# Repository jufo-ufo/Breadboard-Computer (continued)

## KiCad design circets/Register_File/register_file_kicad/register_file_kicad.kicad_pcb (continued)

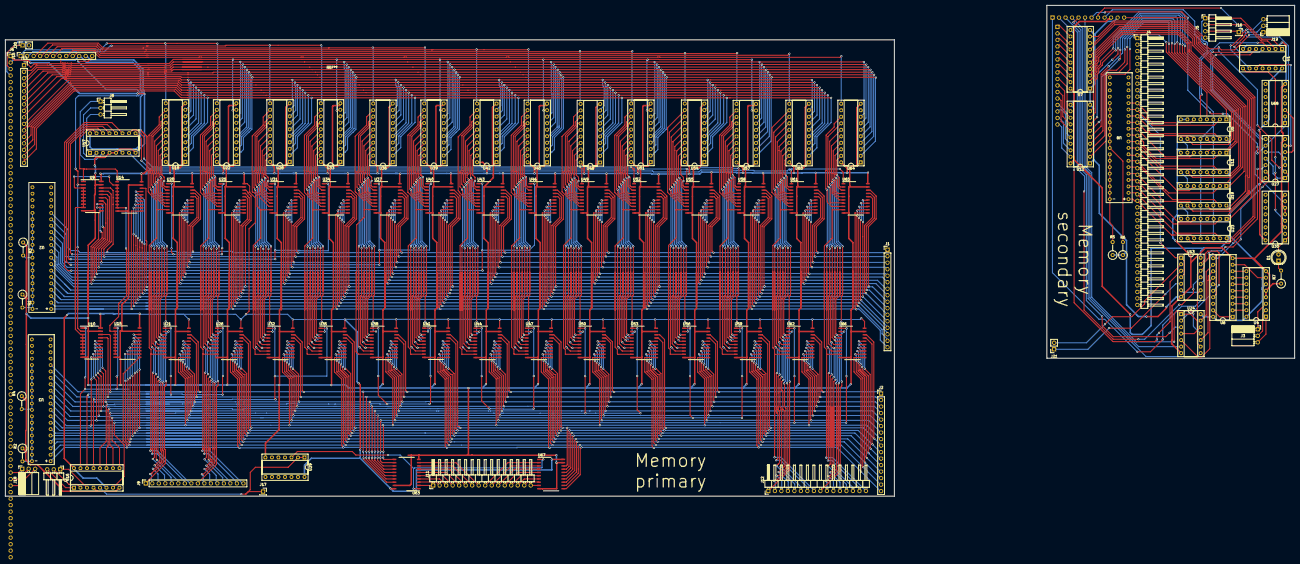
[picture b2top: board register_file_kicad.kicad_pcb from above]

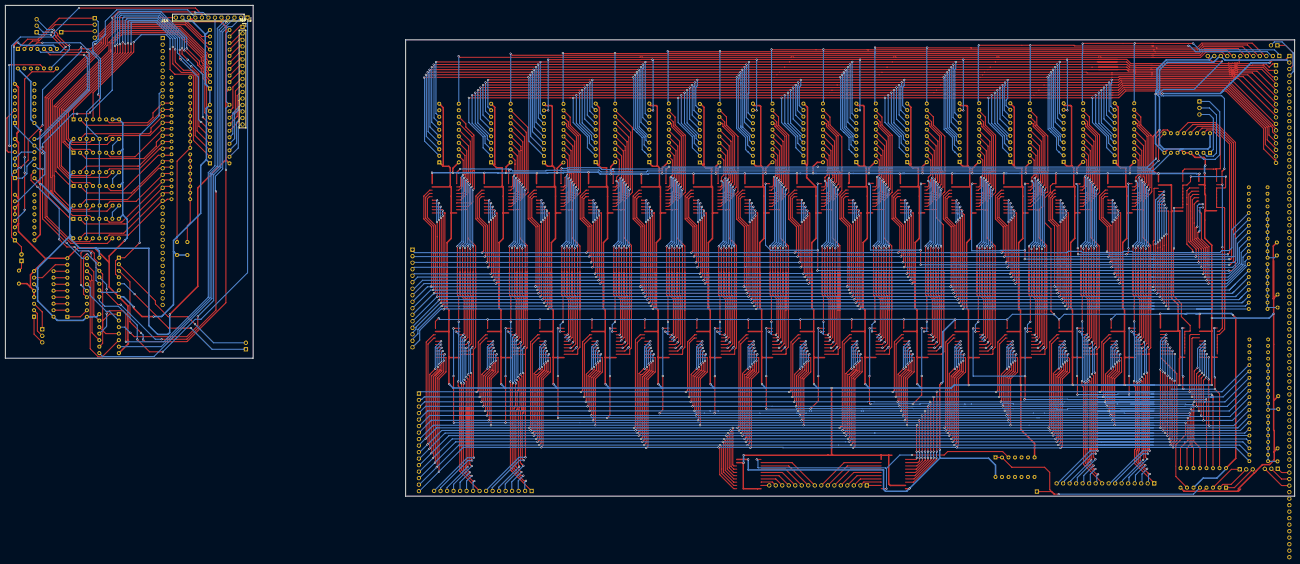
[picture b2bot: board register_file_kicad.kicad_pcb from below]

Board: 2 copper layers, 503.1 x 191.5 mm, 97 parts (2 on the bottom side), 321 nets.

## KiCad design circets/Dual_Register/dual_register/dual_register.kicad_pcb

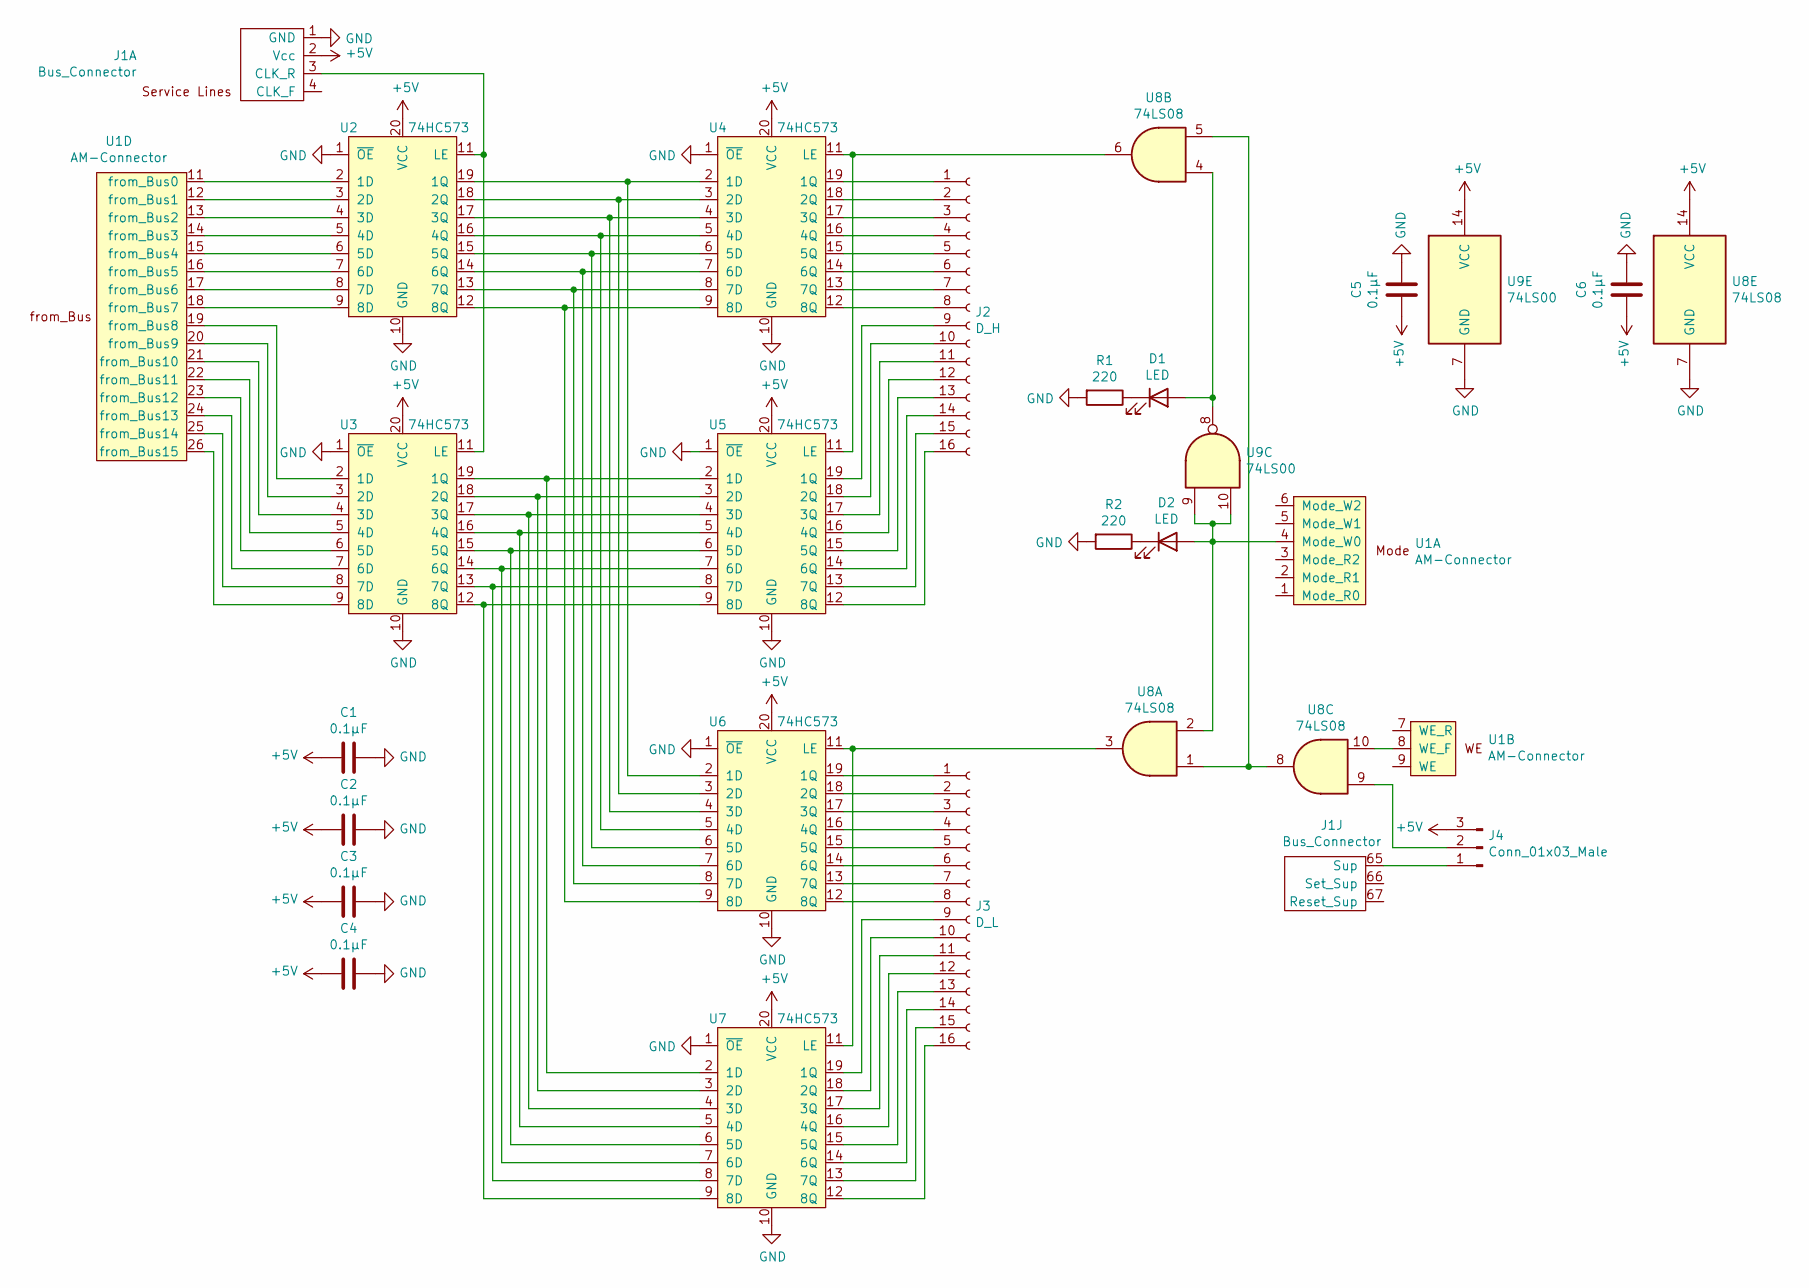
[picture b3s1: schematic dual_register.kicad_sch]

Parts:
C1, C2, C3, C4, C5, C6: 0.1µF; C_Disc_D8.0mm_W5.0mm_P5.00mm
D1, D2: LED; LED_D5.0mm
J1: Bus_Connector; PinHeader_1x78_P2.54mm_Horizontal
J2: D_H; PinHeader_1x16_P2.00mm_Vertical
J3: D_L; PinHeader_1x16_P2.00mm_Vertical
J4: Conn_01x03_Male; PinSocket_1x03_P2.00mm_Vertical
R1, R2: 220; R_Axial_DIN0309_L9.0mm_D3.2mm_P2.54mm_Vertical
U1: AM-Connector; PinHeader_1x42_P2.54mm_Horizontal
U2, U3, U4, U5, U6, U7: 74HC573; DIP-20_W7.62mm_Socket
U8: 74LS08; DIP-14_W7.62mm_Socket
U9: 74LS00; DIP-14_W7.62mm_Socket

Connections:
+5V: C1.2, C2.2, C3.2, C4.2, C5.2, C6.2, J1.2 (Vcc), J4.3, U2.20 (VCC), U3.20 (VCC), U4.20 (VCC), U5.20 (VCC), U6.20 (VCC), U7.20 (VCC), U8.14 (VCC), U9.14 (VCC)
GND: C1.1, C2.1, C3.1, C4.1, C5.1, C6.1, J1.1 (GND), R1.2, R2.2, U2.1 (~OE), U2.10 (GND), U3.1 (~OE), U3.10 (GND), U4.1 (~OE), U4.10 (GND), U5.1 (~OE), U5.10 (GND), U6.1 (~OE), U6.10 (GND), U7.1 (~OE), U7.10 (GND), U8.7 (GND), U9.7 (GND)
unnamed: D1.1 (K), R1.1
unnamed: D1.2 (A), U8.4, U9.8
unnamed: D2.1 (K), R2.1
unnamed: D2.2 (A), U1.4 (Mode_W0), U8.2, U9.9, U9.10
unnamed: J1.3 (CLK_R), U2.11 (LE), U3.11 (LE)
unnamed: J1.65 (Sup), J4.1
unnamed: J2.1, U4.19 (1Q)
unnamed: J2.2, U4.18 (2Q)
unnamed: J2.3, U4.17 (3Q)
unnamed: J2.4, U4.16 (4Q)
unnamed: J2.5, U4.15 (5Q)
unnamed: J2.6, U4.14 (6Q)
unnamed: J2.7, U4.13 (7Q)
unnamed: J2.8, U4.12 (8Q)
unnamed: J2.9, U5.19 (1Q)
unnamed: J2.10, U5.18 (2Q)
unnamed: J2.11, U5.17 (3Q)
unnamed: J2.12, U5.16 (4Q)
unnamed: J2.13, U5.15 (5Q)
unnamed: J2.14, U5.14 (6Q)
unnamed: J2.15, U5.13 (7Q)
unnamed: J2.16, U5.12 (8Q)
unnamed: J3.1, U6.19 (1Q)
unnamed: J3.2, U6.18 (2Q)
unnamed: J3.3, U6.17 (3Q)
unnamed: J3.4, U6.16 (4Q)
unnamed: J3.5, U6.15 (5Q)
unnamed: J3.6, U6.14 (6Q)
unnamed: J3.7, U6.13 (7Q)
unnamed: J3.8, U6.12 (8Q)
unnamed: J3.9, U7.19 (1Q)
unnamed: J3.10, U7.18 (2Q)
unnamed: J3.11, U7.17 (3Q)
unnamed: J3.12, U7.16 (4Q)
unnamed: J3.13, U7.15 (5Q)
unnamed: J3.14, U7.14 (6Q)
unnamed: J3.15, U7.13 (7Q)
unnamed: J3.16, U7.12 (8Q)
unnamed: J4.2, U8.9
unnamed: U1.8 (WE_F), U8.10
unnamed: U1.11 (from_Bus0), U2.2 (1D)
unnamed: U1.12 (from_Bus1), U2.3 (2D)
unnamed: U1.13 (from_Bus2), U2.4 (3D)
unnamed: U1.14 (from_Bus3), U2.5 (4D)
unnamed: U1.15 (from_Bus4), U2.6 (5D)
unnamed: U1.16 (from_Bus5), U2.7 (6D)
unnamed: U1.17 (from_Bus6), U2.8 (7D)
unnamed: U1.18 (from_Bus7), U2.9 (8D)
unnamed: U1.19 (from_Bus8), U3.2 (1D)
unnamed: U1.20 (from_Bus9), U3.3 (2D)
unnamed: U1.21 (from_Bus10), U3.4 (3D)
unnamed: U1.22 (from_Bus11), U3.5 (4D)
unnamed: U1.23 (from_Bus12), U3.6 (5D)
unnamed: U1.24 (from_Bus13), U3.7 (6D)
unnamed: U1.25 (from_Bus14), U3.8 (7D)
unnamed: U1.26 (from_Bus15), U3.9 (8D)
unnamed: U2.12 (8Q), U4.9 (8D), U6.9 (8D)
unnamed: U2.13 (7Q), U4.8 (7D), U6.8 (7D)
unnamed: U2.14 (6Q), U4.7 (6D), U6.7 (6D)
unnamed: U2.15 (5Q), U4.6 (5D), U6.6 (5D)
unnamed: U2.16 (4Q), U4.5 (4D), U6.5 (4D)
unnamed: U2.17 (3Q), U4.4 (3D), U6.4 (3D)
unnamed: U2.18 (2Q), U4.3 (2D), U6.3 (2D)
unnamed: U2.19 (1Q), U4.2 (1D), U6.2 (1D)
unnamed: U3.12 (8Q), U5.9 (8D), U7.9 (8D)
unnamed: U3.13 (7Q), U5.8 (7D), U7.8 (7D)
unnamed: U3.14 (6Q), U5.7 (6D), U7.7 (6D)
unnamed: U3.15 (5Q), U5.6 (5D), U7.6 (5D)
unnamed: U3.16 (4Q), U5.5 (4D), U7.5 (4D)
unnamed: U3.17 (3Q), U5.4 (3D), U7.4 (3D)
unnamed: U3.18 (2Q), U5.3 (2D), U7.3 (2D)
unnamed: U3.19 (1Q), U5.2 (1D), U7.2 (1D)
unnamed: U4.11 (LE), U5.11 (LE), U8.6
unnamed: U6.11 (LE), U7.11 (LE), U8.3
unnamed: U8.1, U8.5, U8.8

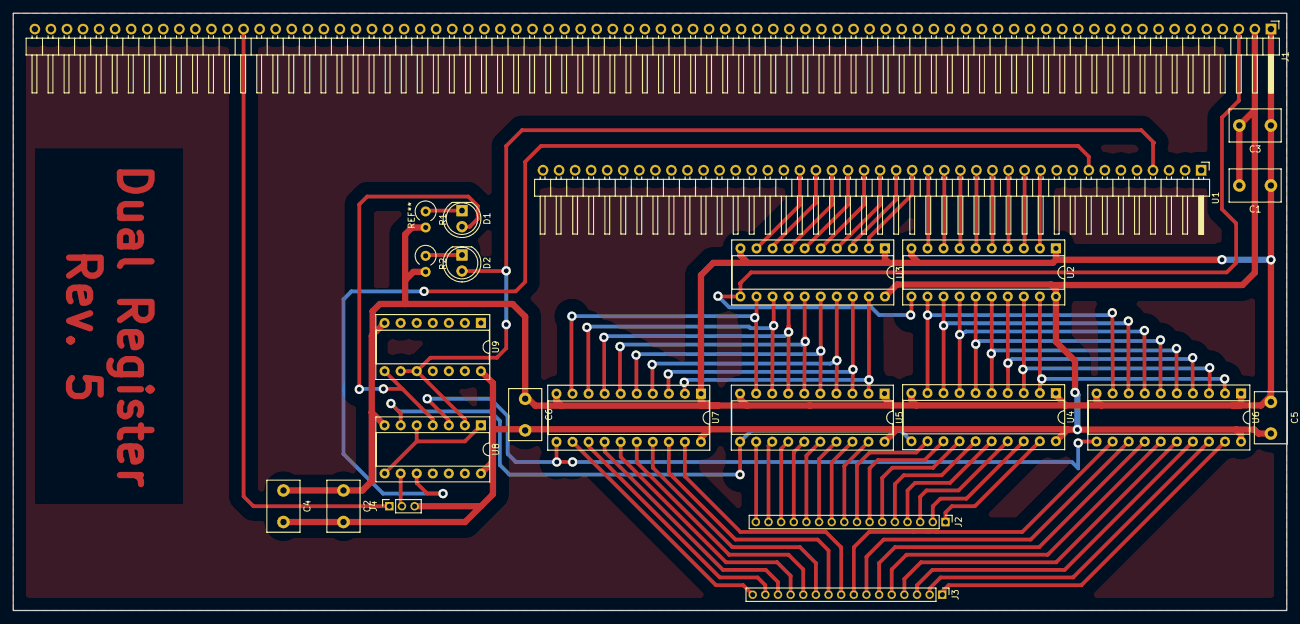
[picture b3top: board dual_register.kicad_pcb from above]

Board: 2 copper layers, 201.5 x 94.5 mm, 23 parts (0 on the bottom side), 77 nets.

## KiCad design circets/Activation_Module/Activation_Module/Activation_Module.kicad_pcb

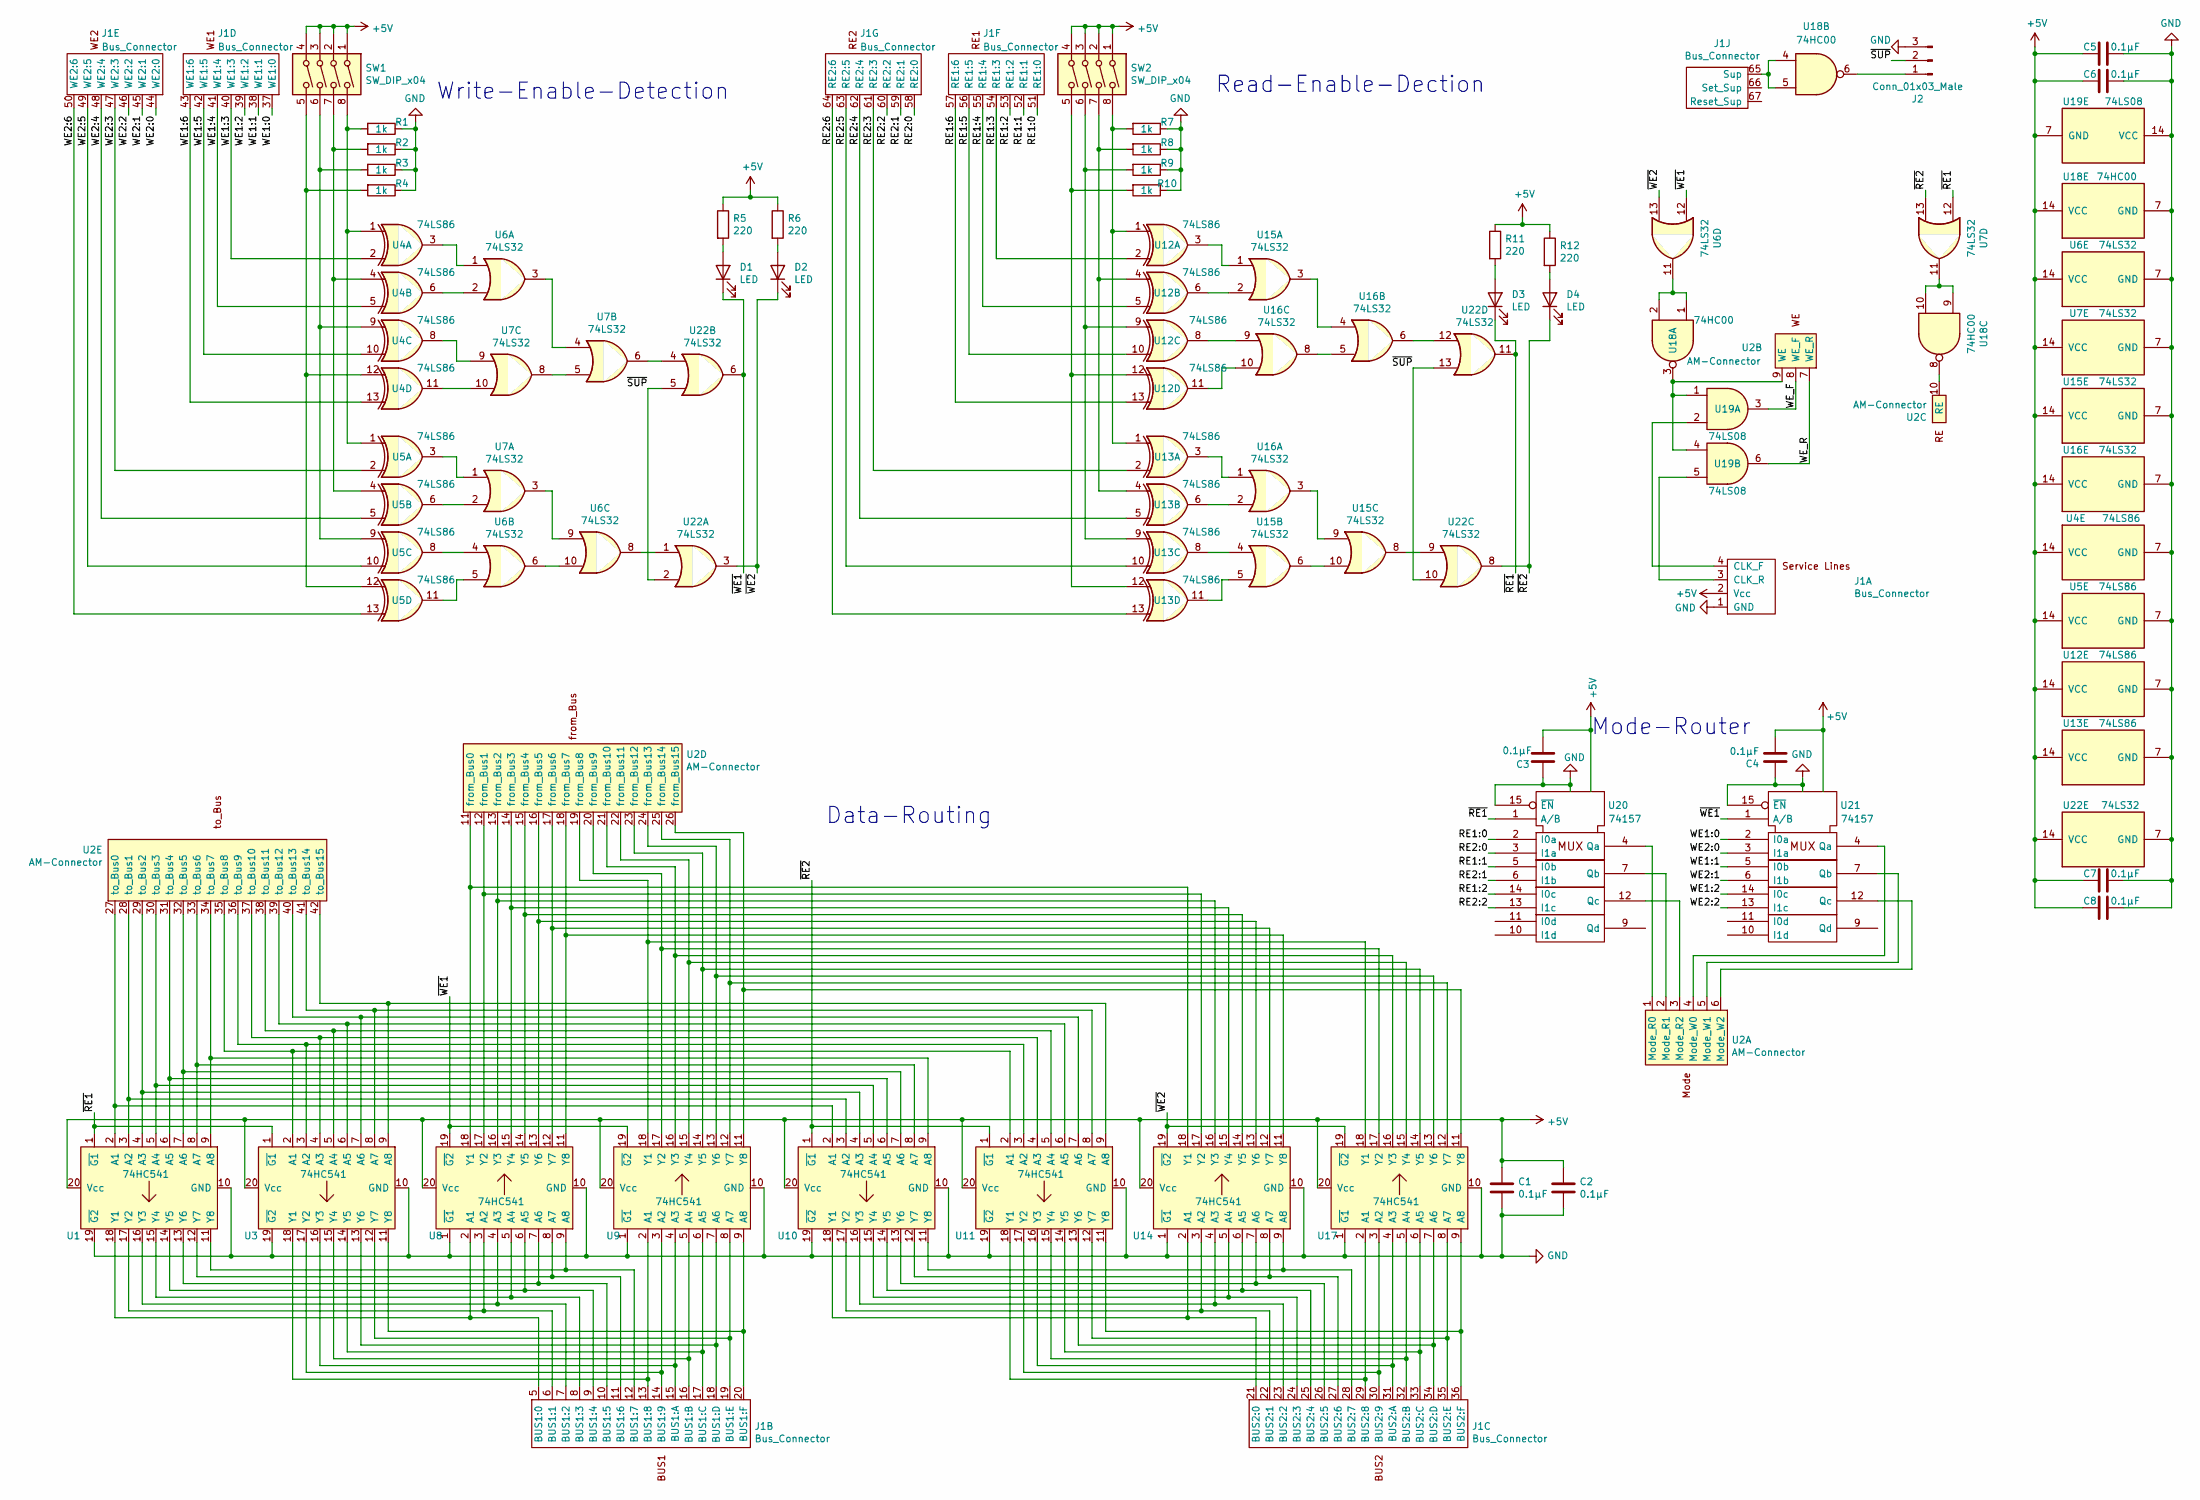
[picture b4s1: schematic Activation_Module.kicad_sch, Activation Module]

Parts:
C1, C2, C3, C4, C5, C6, C7, C8: 0.1µF; C_Disc_D6.0mm_W2.5mm_P5.00mm
D1, D2, D3, D4: LED; LED_D4.0mm
J1: Bus_Connector; PinHeader_1x78_P2.54mm_Horizontal
J2: Conn_01x03_Male; PinSocket_1x03_P2.00mm_Vertical
R1, R2, R3, R4, R7, R8, R9, R10: 1k; R_Axial_DIN0207_L6.3mm_D2.5mm_P2.54mm_Vertical
R5, R6, R11, R12: 220; R_Axial_DIN0207_L6.3mm_D2.5mm_P2.54mm_Vertical
SW1, SW2: SW_DIP_x04; SW_DIP_SPSTx04_Slide_9.78x12.34mm_W7.62mm_P2.54mm
U1, U3, U8, U9, U10, U11, U14, U17: 74HC541; SO-20_12.8x7.5mm_P1.27mm
U2: AM-Connector; PinSocket_1x42_P2.00mm_Horizontal
U4, U5, U12, U13: 74LS86; DIP-14_W7.62mm_Socket
U6, U7, U15, U16, U22: 74LS32; DIP-14_W7.62mm_Socket
U18: 74HC00; DIP-14_W7.62mm_Socket
U19: 74LS08; DIP-14_W7.62mm_Socket
U20, U21: 74157; DIP-16_W7.62mm_Socket

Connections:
+5V: C1.1, C2.1, C3.1, C4.2, C5.2, C6.2, C7.2, C8.2, J1.2 (Vcc), R5.1, R6.1, R11.1, R12.1, SW1.1, SW1.2, SW1.3, SW1.4, SW2.1, SW2.2, SW2.3, SW2.4, U1.20 (Vcc), U3.20 (Vcc), U4.14 (VCC), U5.14 (VCC), U6.14 (VCC), U7.14 (VCC), U8.20 (Vcc), U9.20 (Vcc), U10.20 (Vcc), U11.20 (Vcc), U12.14 (VCC), U13.14 (VCC), U14.20 (Vcc), U15.14 (VCC), U16.14 (VCC), U17.20 (Vcc), U18.14 (VCC), U19.7 (GND), U20.16 (VCC), U21.16 (VCC), U22.14 (VCC)
/RE1:0: J1.51 (RE1:0), U20.2 (I0a)
/RE1:1: J1.52 (RE1:1), U20.5 (I0b)
/RE1:2: J1.53 (RE1:2), U20.14 (I0c)
/RE1:3: J1.54 (RE1:3), U12.2
/RE1:4: J1.55 (RE1:4), U12.5
/RE1:5: J1.56 (RE1:5), U12.10
/RE1:6: J1.57 (RE1:6), U12.13
/RE2:0: J1.58 (RE2:0), U20.3 (I1a)
/RE2:1: J1.59 (RE2:1), U20.6 (I1b)
/RE2:2: J1.60 (RE2:2), U20.13 (I1c)
/RE2:3: J1.61 (RE2:3), U13.2
/RE2:4: J1.62 (RE2:4), U13.5
/RE2:5: J1.63 (RE2:5), U13.10
/RE2:6: J1.64 (RE2:6), U13.13
/WE1:0: J1.37 (WE1:0), U21.2 (I0a)
/WE1:1: J1.38 (WE1:1), U21.5 (I0b)
/WE1:2: J1.39 (WE1:2), U21.14 (I0c)
/WE1:3: J1.40 (WE1:3), U4.2
/WE1:4: J1.41 (WE1:4), U4.5
/WE1:5: J1.42 (WE1:5), U4.10
/WE1:6: J1.43 (WE1:6), U4.13
/WE2:0: J1.44 (WE2:0), U21.3 (I1a)
/WE2:1: J1.45 (WE2:1), U21.6 (I1b)
/WE2:2: J1.46 (WE2:2), U21.13 (I1c)
/WE2:3: J1.47 (WE2:3), U5.2
/WE2:4: J1.48 (WE2:4), U5.5
/WE2:5: J1.49 (WE2:5), U5.10
/WE2:6: J1.50 (WE2:6), U5.13
/WE_F: U2.8 (WE_F), U19.3
/WE_R: U2.7 (WE_R), U19.6
/~RE1: D3.1 (K), U1.1 (~G1), U3.1 (~G1), U7.12, U20.1 (A/B), U22.11
/~RE2: D4.1 (K), U7.13, U10.1 (~G1), U11.1 (~G1), U22.8
/~SUP: J2.2, U22.2, U22.5, U22.10, U22.13
/~WE1: D1.1 (K), U6.12, U8.19 (~G2), U9.19 (~G2), U21.1 (A/B), U22.6
/~WE2: D2.1 (K), U6.13, U14.19 (~G2), U17.19 (~G2), U22.3
GND: C1.2, C2.2, C3.2, C4.1, C5.1, C6.1, C7.1, C8.1, J1.1 (GND), J2.3, R1.1, R2.1, R3.1, R4.1, R7.1, R8.1, R9.1, R10.1, U1.10 (GND), U1.19 (~G2), U3.10 (GND), U3.19 (~G2), U4.7 (GND), U5.7 (GND), U6.7 (GND), U7.7 (GND), U8.1 (~G1), U8.10 (GND), U9.1 (~G1), U9.10 (GND), U10.10 (GND), U10.19 (~G2), U11.10 (GND), U11.19 (~G2), U12.7 (GND), U13.7 (GND), U14.1 (~G1), U14.10 (GND), U15.7 (GND), U16.7 (GND), U17.1 (~G1), U17.10 (GND), U18.7 (GND), U19.14 (VCC), U20.8 (GND), U20.15 (~EN), U21.8 (GND), U21.15 (~EN), U22.7 (GND)
unnamed: D1.2 (A), R5.2
unnamed: D2.2 (A), R6.2
unnamed: D3.2 (A), R11.2
unnamed: D4.2 (A), R12.2
unnamed: J1.3 (CLK_R), U19.5
unnamed: J1.4 (CLK_F), U19.2
unnamed: J1.5 (BUS1:0), U1.18 (Y1), U8.2 (A1)
unnamed: J1.6 (BUS1:1), U1.17 (Y2), U8.3 (A2)
unnamed: J1.7 (BUS1:2), U1.16 (Y3), U8.4 (A3)
unnamed: J1.8 (BUS1:3), U1.15 (Y4), U8.5 (A4)
unnamed: J1.9 (BUS1:4), U1.14 (Y5), U8.6 (A5)
unnamed: J1.10 (BUS1:5), U1.13 (Y6), U8.7 (A6)
unnamed: J1.11 (BUS1:6), U1.12 (Y7), U8.8 (A7)
unnamed: J1.12 (BUS1:7), U1.11 (Y8), U8.9 (A8)
unnamed: J1.13 (BUS1:8), U3.18 (Y1), U9.2 (A1)
unnamed: J1.14 (BUS1:9), U3.17 (Y2), U9.3 (A2)
unnamed: J1.15 (BUS1:A), U3.16 (Y3), U9.4 (A3)
unnamed: J1.16 (BUS1:B), U3.15 (Y4), U9.5 (A4)
unnamed: J1.17 (BUS1:C), U3.14 (Y5), U9.6 (A5)
unnamed: J1.18 (BUS1:D), U3.13 (Y6), U9.7 (A6)
unnamed: J1.19 (BUS1:E), U3.12 (Y7), U9.8 (A7)
unnamed: J1.20 (BUS1:F), U3.11 (Y8), U9.9 (A8)
unnamed: J1.21 (BUS2:0), U10.18 (Y1), U14.2 (A1)
unnamed: J1.22 (BUS2:1), U10.17 (Y2), U14.3 (A2)
unnamed: J1.23 (BUS2:2), U10.16 (Y3), U14.4 (A3)
unnamed: J1.24 (BUS2:3), U10.15 (Y4), U14.5 (A4)
unnamed: J1.25 (BUS2:4), U10.14 (Y5), U14.6 (A5)
unnamed: J1.26 (BUS2:5), U10.13 (Y6), U14.7 (A6)
unnamed: J1.27 (BUS2:6), U10.12 (Y7), U14.8 (A7)
unnamed: J1.28 (BUS2:7), U10.11 (Y8), U14.9 (A8)
unnamed: J1.29 (BUS2:8), U11.18 (Y1), U17.2 (A1)
unnamed: J1.30 (BUS2:9), U11.17 (Y2), U17.3 (A2)
unnamed: J1.31 (BUS2:A), U11.16 (Y3), U17.4 (A3)
unnamed: J1.32 (BUS2:B), U11.15 (Y4), U17.5 (A4)
unnamed: J1.33 (BUS2:C), U11.14 (Y5), U17.6 (A5)
unnamed: J1.34 (BUS2:D), U11.13 (Y6), U17.7 (A6)
unnamed: J1.35 (BUS2:E), U11.12 (Y7), U17.8 (A7)
unnamed: J1.36 (BUS2:F), U11.11 (Y8), U17.9 (A8)
unnamed: J1.65 (Sup), U18.4, U18.5
unnamed: J2.1, U18.6
unnamed: R1.2, SW1.8, U4.1, U5.1
unnamed: R2.2, SW1.7, U4.4, U5.4
unnamed: R3.2, SW1.6, U4.9, U5.9
unnamed: R4.2, SW1.5, U4.12, U5.12
unnamed: R7.2, SW2.8, U12.1, U13.1
unnamed: R8.2, SW2.7, U12.4, U13.4
unnamed: R9.2, SW2.6, U12.9, U13.9
unnamed: R10.2, SW2.5, U12.12, U13.12
unnamed: U1.2 (A1), U2.27 (to_Bus0), U10.2 (A1)
unnamed: U1.3 (A2), U2.28 (to_Bus1), U10.3 (A2)
unnamed: U1.4 (A3), U2.29 (to_Bus2), U10.4 (A3)
unnamed: U1.5 (A4), U2.30 (to_Bus3), U10.5 (A4)
unnamed: U1.6 (A5), U2.31 (to_Bus4), U10.6 (A5)
unnamed: U1.7 (A6), U2.32 (to_Bus5), U10.7 (A6)
unnamed: U1.8 (A7), U2.33 (to_Bus6), U10.8 (A7)
unnamed: U1.9 (A8), U2.34 (to_Bus7), U10.9 (A8)
unnamed: U2.1 (Mode_R0), U20.4 (Qa)
unnamed: U2.2 (Mode_R1), U20.7 (Qb)
unnamed: U2.3 (Mode_R2), U20.12 (Qc)
unnamed: U2.4 (Mode_W0), U21.4 (Qa)
unnamed: U2.5 (Mode_W1), U21.7 (Qb)
unnamed: U2.6 (Mode_W2), U21.12 (Qc)
unnamed: U4.3, U6.1
unnamed: U4.6, U6.2
unnamed: U4.8, U7.9
unnamed: U4.11, U7.10
unnamed: U5.3, U7.1
unnamed: U5.6, U7.2
unnamed: U5.8, U6.4
unnamed: U5.11, U6.5
unnamed: U6.3, U7.4
unnamed: U6.9, U7.3
unnamed: U6.6, U6.10
unnamed: U7.5, U7.8
unnamed: U2.35 (to_Bus8), U3.2 (A1), U11.2 (A1)
unnamed: U2.36 (to_Bus9), U3.3 (A2), U11.3 (A2)
unnamed: U2.37 (to_Bus10), U3.4 (A3), U11.4 (A3)
unnamed: U2.38 (to_Bus11), U3.5 (A4), U11.5 (A4)
unnamed: U2.39 (to_Bus12), U3.6 (A5), U11.6 (A5)
unnamed: U2.40 (to_Bus13), U3.7 (A6), U11.7 (A6)
unnamed: U2.41 (to_Bus14), U3.8 (A7), U11.8 (A7)
unnamed: U2.42 (to_Bus15), U3.9 (A8), U11.9 (A8)
unnamed: U12.3, U15.1
unnamed: U12.6, U15.2
unnamed: U12.8, U16.9
unnamed: U12.11, U16.10
unnamed: U13.3, U16.1
unnamed: U13.6, U16.2
unnamed: U13.8, U15.4
unnamed: U13.11, U15.5
unnamed: U2.18 (from_Bus7), U8.11 (Y8), U14.11 (Y8)
unnamed: U2.17 (from_Bus6), U8.12 (Y7), U14.12 (Y7)
unnamed: U2.16 (from_Bus5), U8.13 (Y6), U14.13 (Y6)
unnamed: U2.15 (from_Bus4), U8.14 (Y5), U14.14 (Y5)
unnamed: U2.14 (from_Bus3), U8.15 (Y4), U14.15 (Y4)
unnamed: U2.13 (from_Bus2), U8.16 (Y3), U14.16 (Y3)
unnamed: U2.12 (from_Bus1), U8.17 (Y2), U14.17 (Y2)
unnamed: U2.11 (from_Bus0), U8.18 (Y1), U14.18 (Y1)
unnamed: U15.3, U16.4
unnamed: U15.8, U22.9
unnamed: U15.9, U16.3
unnamed: U15.6, U15.10
unnamed: U16.5, U16.8
unnamed: U16.6, U22.12
unnamed: U2.26 (from_Bus15), U9.11 (Y8), U17.11 (Y8)
unnamed: U2.25 (from_Bus14), U9.12 (Y7), U17.12 (Y7)
unnamed: U2.24 (from_Bus13), U9.13 (Y6), U17.13 (Y6)
unnamed: U2.23 (from_Bus12), U9.14 (Y5), U17.14 (Y5)
unnamed: U2.22 (from_Bus11), U9.15 (Y4), U17.15 (Y4)
unnamed: U2.21 (from_Bus10), U9.16 (Y3), U17.16 (Y3)
unnamed: U2.20 (from_Bus9), U9.17 (Y2), U17.17 (Y2)
unnamed: U2.19 (from_Bus8), U9.18 (Y1), U17.18 (Y1)
unnamed: U6.11, U18.1, U18.2
unnamed: U2.9 (WE), U18.3, U19.1, U19.4
unnamed: U2.10 (RE), U18.8
unnamed: U7.11, U18.9, U18.10
unnamed: U6.8, U22.1
unnamed: U7.6, U22.4

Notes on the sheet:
Mode-Router
Data-Routing
Write-Enable-Detection
Read-Enable-Dection

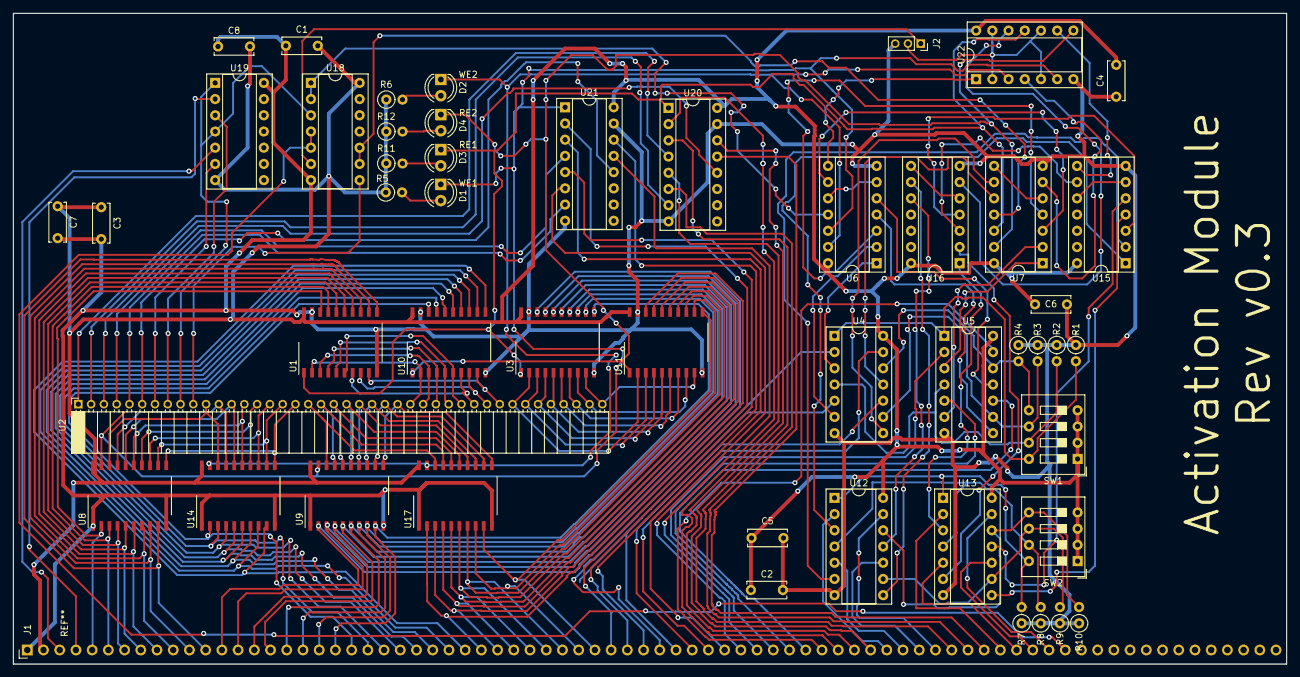
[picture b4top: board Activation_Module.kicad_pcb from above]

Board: 2 copper layers, 199.4 x 101.9 mm, 50 parts (0 on the bottom side), 155 nets.

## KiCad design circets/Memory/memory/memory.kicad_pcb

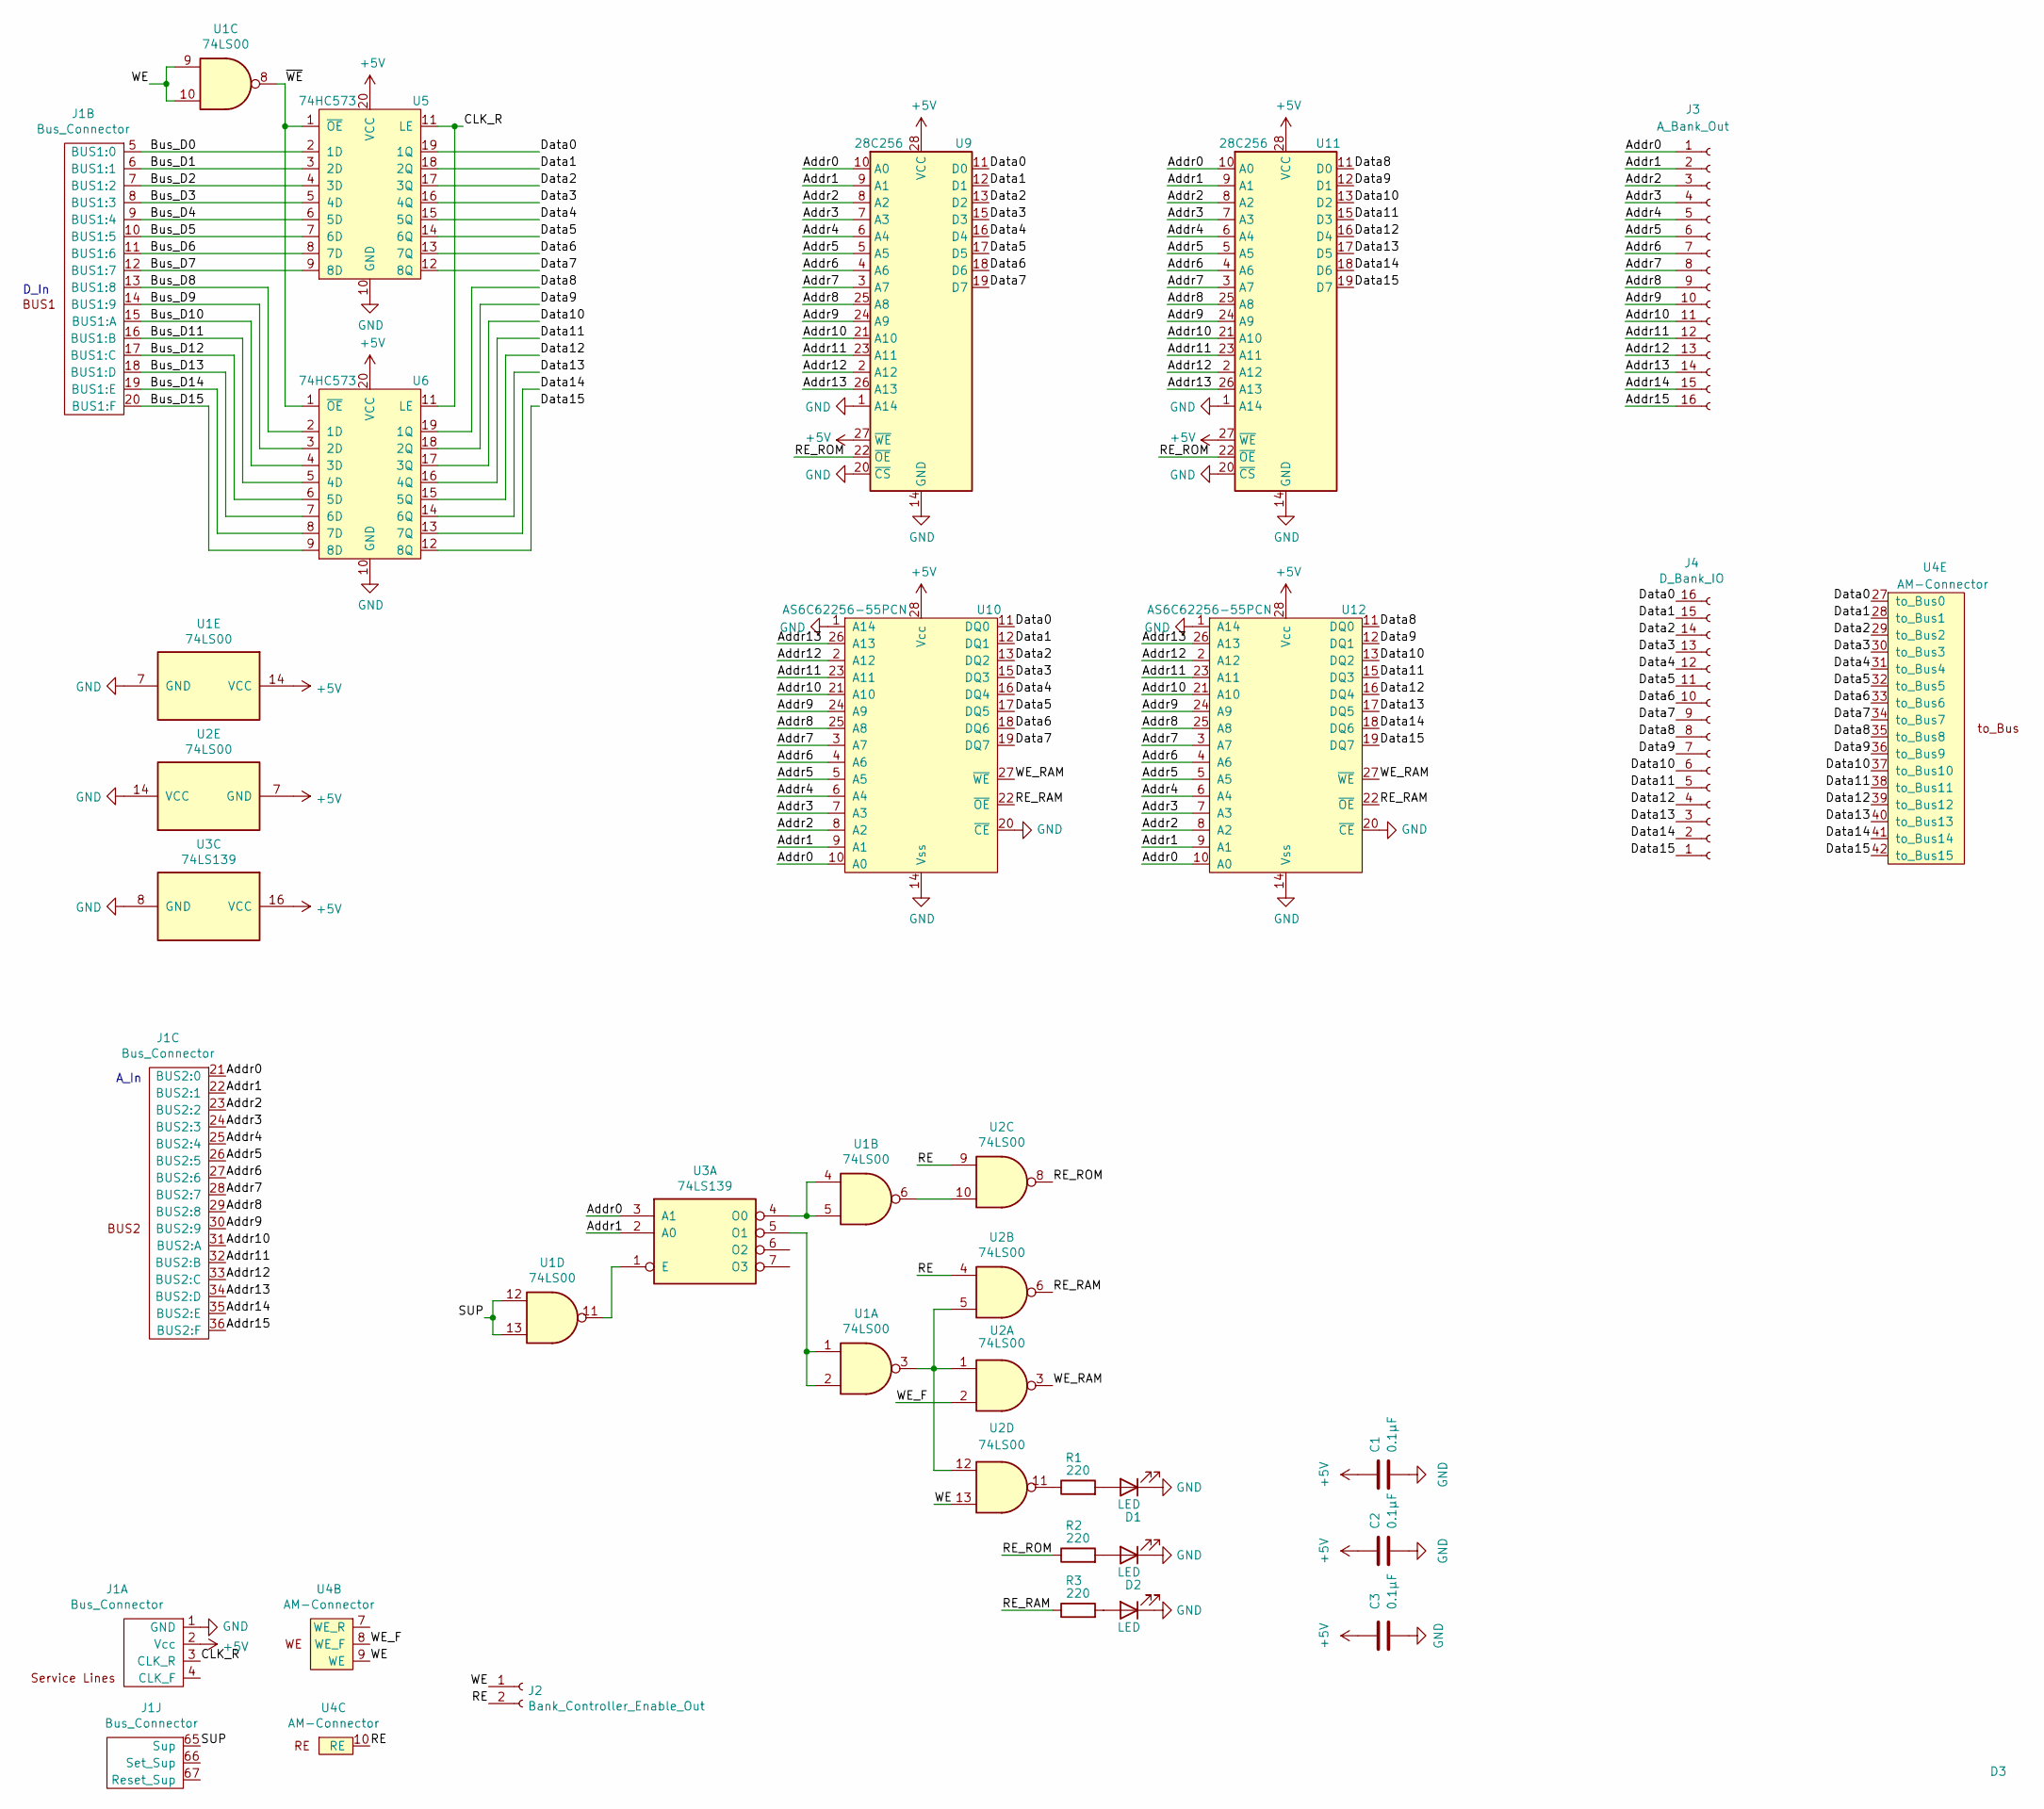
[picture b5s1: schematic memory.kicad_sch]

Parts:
C1, C2, C3: 0.1µF; C_Disc_D8.0mm_W5.0mm_P5.00mm
D1, D2, D3: LED; LED_D5.0mm
J1: Bus_Connector; PinHeader_1x78_P2.54mm_Horizontal
J2: Bank_Controller_Enable_Out; PinSocket_1x02_P2.54mm_Horizontal
J3: A_Bank_Out; PinSocket_1x16_P2.54mm_Horizontal
J4: D_Bank_IO; PinSocket_1x16_P2.54mm_Horizontal
R1, R2, R3: 220; R_Axial_DIN0309_L9.0mm_D3.2mm_P2.54mm_Vertical
U1, U2: 74LS00; DIP-14_W7.62mm_Socket
U3: 74LS139; DIP-16_W7.62mm_Socket
U4: AM-Connector; PinHeader_1x42_P2.54mm_Horizontal
U5, U6: 74HC573; DIP-20_W7.62mm_Socket
U9, U11: 28C256; DIP-28_W15.24mm_Socket
U10, U12: AS6C62256-55PCN; DIP-28_W15.24mm_Socket

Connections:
+5V: C1.1, C2.1, C3.1, J1.2 (Vcc), U1.14 (VCC), U2.7 (GND), U3.16 (VCC), U5.20 (VCC), U6.20 (VCC), U9.27 (~WE), U9.28 (VCC), U10.28 (Vcc), U11.27 (~WE), U11.28 (VCC), U12.28 (Vcc)
/Addr0: J1.21 (BUS2:0), J3.1, U3.3 (A1), U9.10 (A0), U10.10 (A0), U11.10 (A0), U12.10 (A0)
/Addr1: J1.22 (BUS2:1), J3.2, U3.2 (A0), U9.9 (A1), U10.9 (A1), U11.9 (A1), U12.9 (A1)
/Addr2: J1.23 (BUS2:2), J3.3, U9.8 (A2), U10.8 (A2), U11.8 (A2), U12.8 (A2)
/Addr3: J1.24 (BUS2:3), J3.4, U9.7 (A3), U10.7 (A3), U11.7 (A3), U12.7 (A3)
/Addr4: J1.25 (BUS2:4), J3.5, U9.6 (A4), U10.6 (A4), U11.6 (A4), U12.6 (A4)
/Addr5: J1.26 (BUS2:5), J3.6, U9.5 (A5), U10.5 (A5), U11.5 (A5), U12.5 (A5)
/Addr6: J1.27 (BUS2:6), J3.7, U9.4 (A6), U10.4 (A6), U11.4 (A6), U12.4 (A6)
/Addr7: J1.28 (BUS2:7), J3.8, U9.3 (A7), U10.3 (A7), U11.3 (A7), U12.3 (A7)
/Addr8: J1.29 (BUS2:8), J3.9, U9.25 (A8), U10.25 (A8), U11.25 (A8), U12.25 (A8)
/Addr9: J1.30 (BUS2:9), J3.10, U9.24 (A9), U10.24 (A9), U11.24 (A9), U12.24 (A9)
/Addr10: J1.31 (BUS2:A), J3.11, U9.21 (A10), U10.21 (A10), U11.21 (A10), U12.21 (A10)
/Addr11: J1.32 (BUS2:B), J3.12, U9.23 (A11), U10.23 (A11), U11.23 (A11), U12.23 (A11)
/Addr12: J1.33 (BUS2:C), J3.13, U9.2 (A12), U10.2 (A12), U11.2 (A12), U12.2 (A12)
/Addr13: J1.34 (BUS2:D), J3.14, U9.26 (A13), U10.26 (A13), U11.26 (A13), U12.26 (A13)
/Addr14: J1.35 (BUS2:E), J3.15
/Addr15: J1.36 (BUS2:F), J3.16
/Bus_D0: J1.5 (BUS1:0), U5.2 (1D)
/Bus_D1: J1.6 (BUS1:1), U5.3 (2D)
/Bus_D2: J1.7 (BUS1:2), U5.4 (3D)
/Bus_D3: J1.8 (BUS1:3), U5.5 (4D)
/Bus_D4: J1.9 (BUS1:4), U5.6 (5D)
/Bus_D5: J1.10 (BUS1:5), U5.7 (6D)
/Bus_D6: J1.11 (BUS1:6), U5.8 (7D)
/Bus_D7: J1.12 (BUS1:7), U5.9 (8D)
/Bus_D8: J1.13 (BUS1:8), U6.2 (1D)
/Bus_D9: J1.14 (BUS1:9), U6.3 (2D)
/Bus_D10: J1.15 (BUS1:A), U6.4 (3D)
/Bus_D11: J1.16 (BUS1:B), U6.5 (4D)
/Bus_D12: J1.17 (BUS1:C), U6.6 (5D)
/Bus_D13: J1.18 (BUS1:D), U6.7 (6D)
/Bus_D14: J1.19 (BUS1:E), U6.8 (7D)
/Bus_D15: J1.20 (BUS1:F), U6.9 (8D)
/CLK_R: J1.3 (CLK_R), U5.11 (LE), U6.11 (LE)
/Data0: J4.16, U4.27 (to_Bus0), U5.19 (1Q), U9.11 (D0), U10.11 (DQ0)
/Data1: J4.15, U4.28 (to_Bus1), U5.18 (2Q), U9.12 (D1), U10.12 (DQ1)
/Data2: J4.14, U4.29 (to_Bus2), U5.17 (3Q), U9.13 (D2), U10.13 (DQ2)
/Data3: J4.13, U4.30 (to_Bus3), U5.16 (4Q), U9.15 (D3), U10.15 (DQ3)
/Data4: J4.12, U4.31 (to_Bus4), U5.15 (5Q), U9.16 (D4), U10.16 (DQ4)
/Data5: J4.11, U4.32 (to_Bus5), U5.14 (6Q), U9.17 (D5), U10.17 (DQ5)
/Data6: J4.10, U4.33 (to_Bus6), U5.13 (7Q), U9.18 (D6), U10.18 (DQ6)
/Data7: J4.9, U4.34 (to_Bus7), U5.12 (8Q), U9.19 (D7), U10.19 (DQ7)
/Data8: J4.8, U4.35 (to_Bus8), U6.19 (1Q), U11.11 (D0), U12.11 (DQ0)
/Data9: J4.7, U4.36 (to_Bus9), U6.18 (2Q), U11.12 (D1), U12.12 (DQ1)
/Data10: J4.6, U4.37 (to_Bus10), U6.17 (3Q), U11.13 (D2), U12.13 (DQ2)
/Data11: J4.5, U4.38 (to_Bus11), U6.16 (4Q), U11.15 (D3), U12.15 (DQ3)
/Data12: J4.4, U4.39 (to_Bus12), U6.15 (5Q), U11.16 (D4), U12.16 (DQ4)
/Data13: J4.3, U4.40 (to_Bus13), U6.14 (6Q), U11.17 (D5), U12.17 (DQ5)
/Data14: J4.2, U4.41 (to_Bus14), U6.13 (7Q), U11.18 (D6), U12.18 (DQ6)
/Data15: J4.1, U4.42 (to_Bus15), U6.12 (8Q), U11.19 (D7), U12.19 (DQ7)
/RE: J2.2, U2.4, U2.9, U4.10 (RE)
/RE_RAM: R3.1, U2.6, U10.22 (~OE), U12.22 (~OE)
/RE_ROM: R2.1, U2.8, U9.22 (~OE), U11.22 (~OE)
/SUP: J1.65 (Sup), U1.12, U1.13
/WE: J2.1, U1.9, U1.10, U2.13, U4.9 (WE)
/WE_F: U2.2, U4.8 (WE_F)
/WE_RAM: U2.3, U10.27 (~WE), U12.27 (~WE)
/~WE: U1.8, U5.1 (~OE), U6.1 (~OE)
GND: C1.2, C2.2, C3.2, D1.1 (K), D2.1 (K), D3.1 (K), J1.1 (GND), U1.7 (GND), U2.14 (VCC), U3.8 (GND), U5.10 (GND), U6.10 (GND), U9.1 (A14), U9.14 (GND), U9.20 (~CS), U10.1 (A14), U10.14 (Vss), U10.20 (~CE), U11.1 (A14), U11.14 (GND), U11.20 (~CS), U12.1 (A14), U12.14 (Vss), U12.20 (~CE)
unnamed: D1.2 (A), R1.2
unnamed: D2.2 (A), R2.2
unnamed: D3.2 (A), R3.2
unnamed: U1.1, U1.2, U3.5 (O1)
unnamed: U1.3, U2.1, U2.5, U2.12
unnamed: U1.4, U1.5, U3.4 (O0)
unnamed: U1.6, U2.10
unnamed: U1.11, U3.1 (E)
unnamed: R1.1, U2.11

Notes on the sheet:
D_In
A_In
